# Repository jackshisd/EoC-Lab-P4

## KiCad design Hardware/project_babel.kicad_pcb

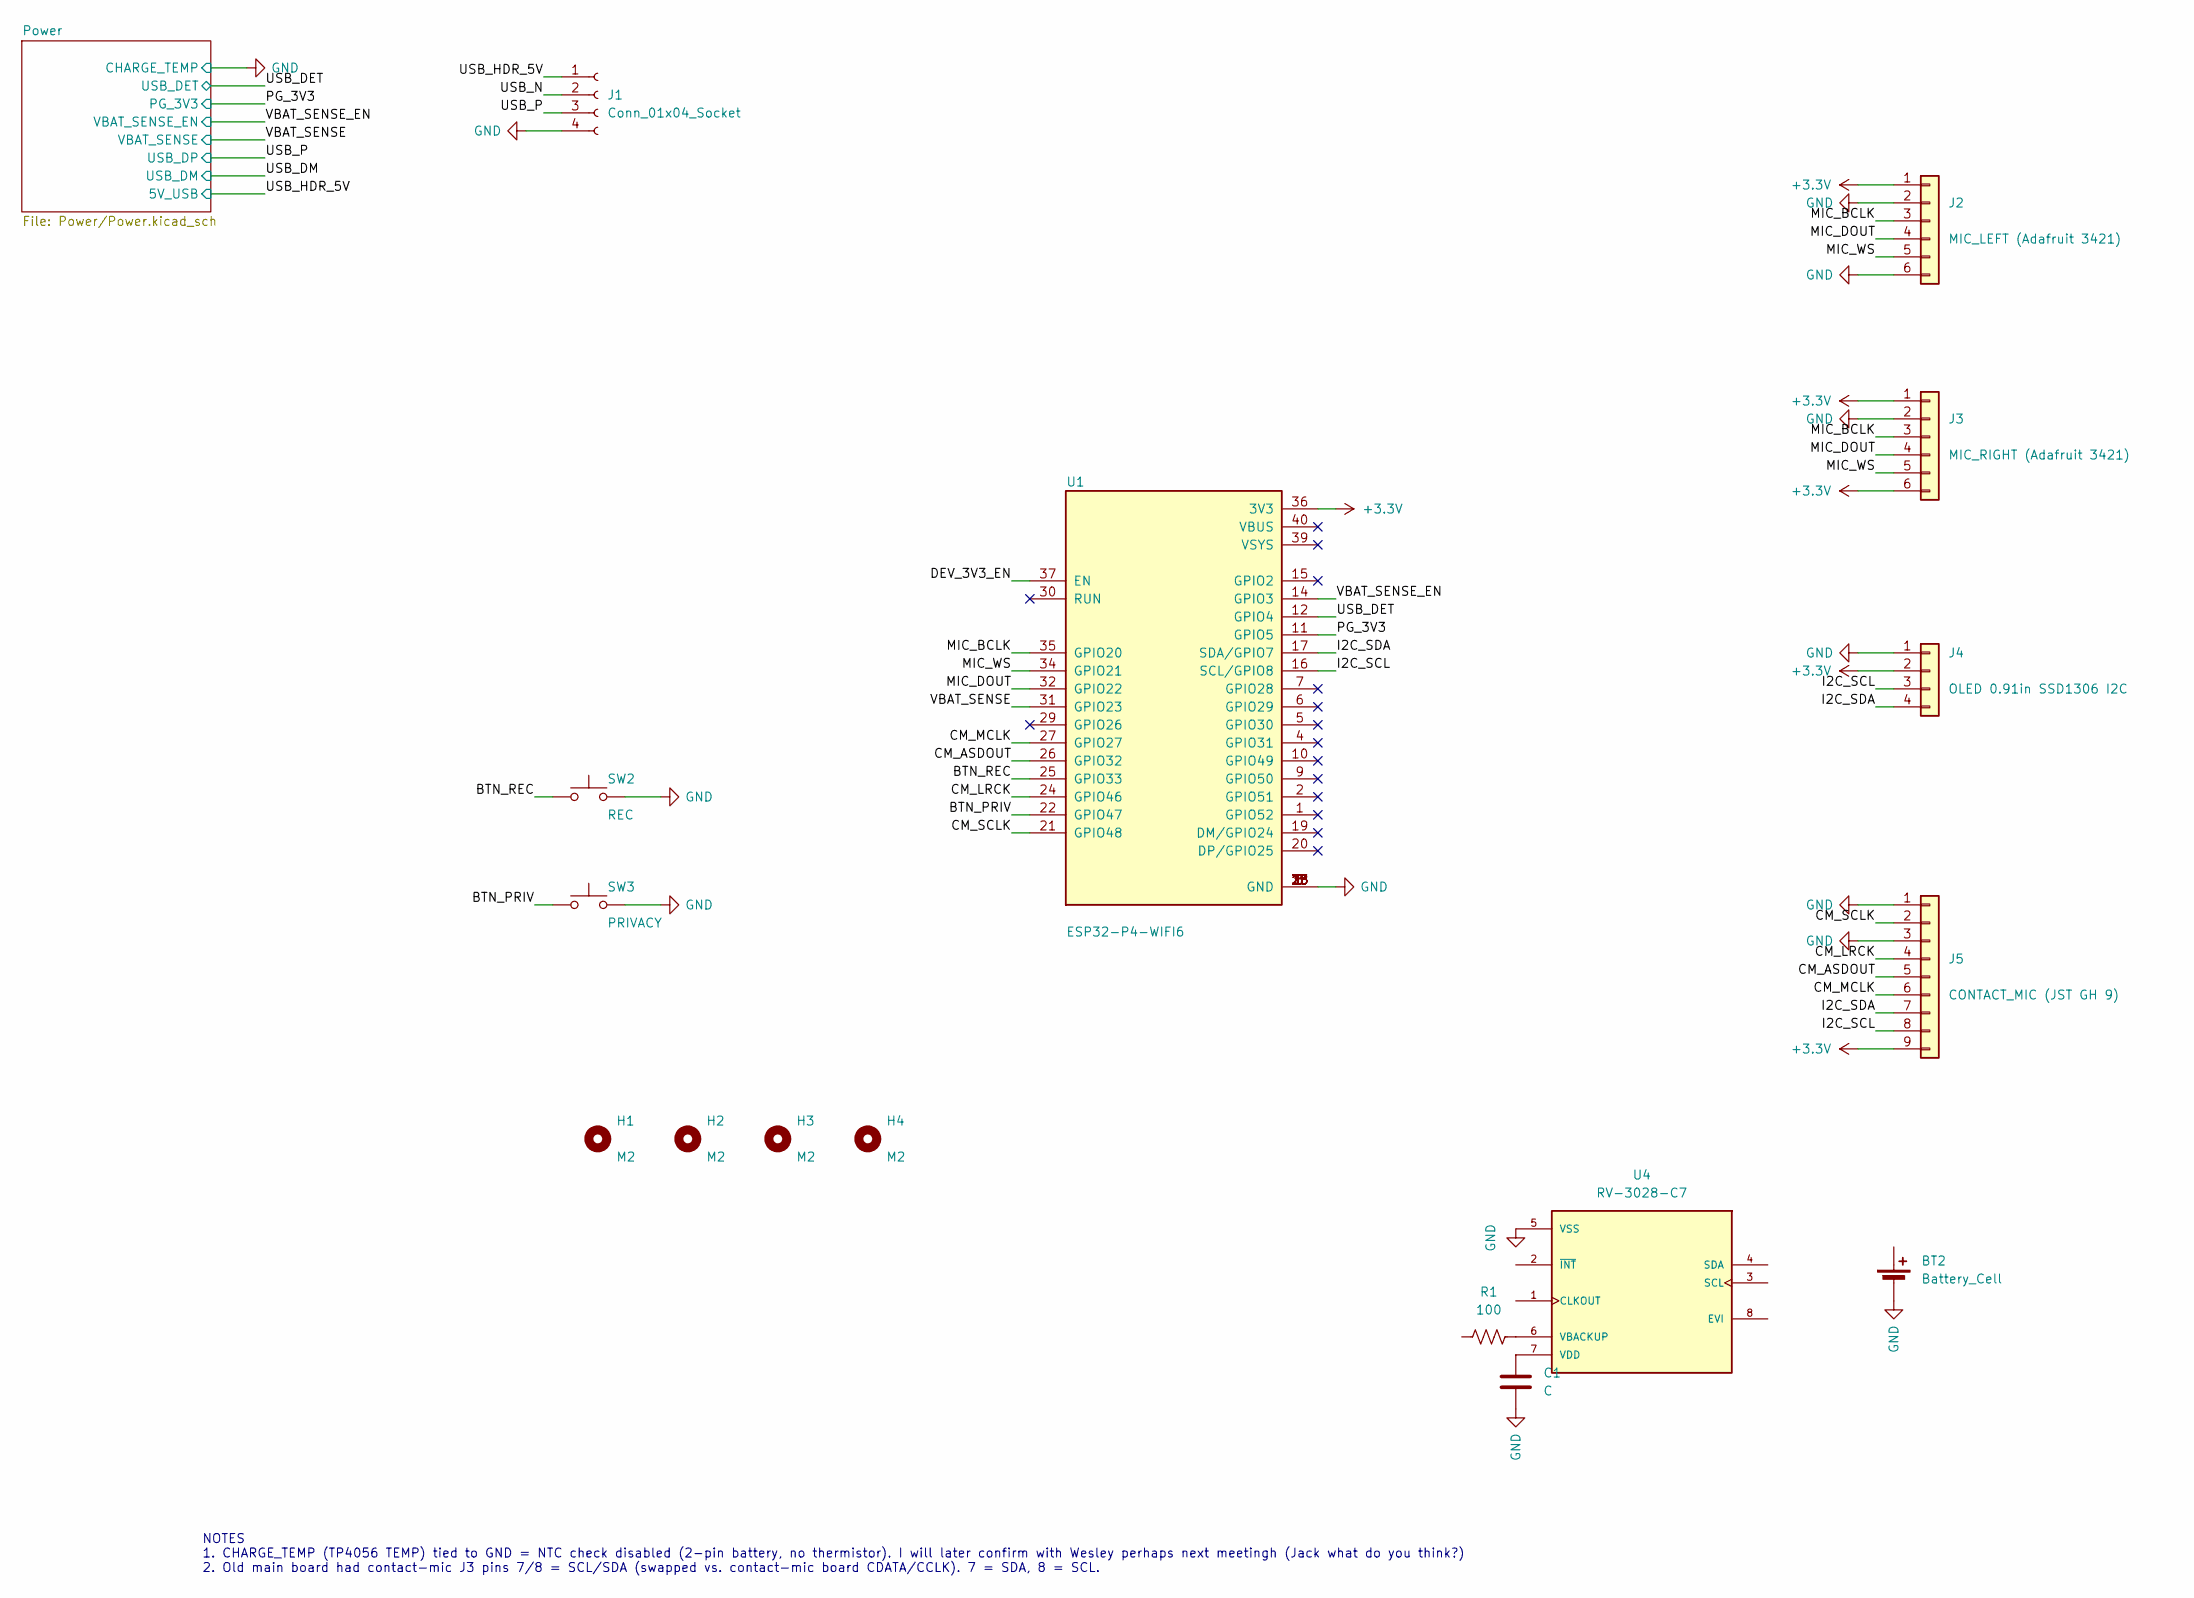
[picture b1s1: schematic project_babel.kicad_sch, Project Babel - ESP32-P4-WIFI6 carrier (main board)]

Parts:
BT2: Battery_Cell; BatteryHolder_Keystone_3000_1x12mm
C1: C
H1, H2, H3, H4: M2; MountingHole_2.2mm_M2
J1: Conn_01x04_Socket; PinHeader_1x04_P1.27mm_Vertical
J2: MIC_LEFT (Adafruit 3421); Adafruit_I2S_MEMS_Mic_Breakout_1x06_P2.54mm; MPN Adafruit 3421
J3: MIC_RIGHT (Adafruit 3421); Adafruit_I2S_MEMS_Mic_Breakout_1x06_P2.54mm; MPN Adafruit 3421
J4: OLED 0.91in SSD1306 I2C; SSD1306-0.91-OLED-4pin-128x32
J5: CONTACT_MIC (JST GH 9); JST_GH_SM09B-GHS-TB_1x09-1MP_P1.25mm_Horizontal; MPN JST SM09B-GHS-TB(LF)(SN)
R1: 100
SW2: REC; SW_SPST_PTS645Sx43SMTR92; MPN C&K PTS645SM43SMTR92 LFS (6x6 SMD)
SW3: PRIVACY; SW_SPST_PTS645Sx43SMTR92; MPN C&K PTS645SM43SMTR92 LFS (6x6 SMD)
U1: ESP32-P4-WIFI6; MODULE_ESP32-P4-WIFI6; MPN ESP32-P4-WIFI6
U4: RV-3028-C7; IC_RV-3028-C7; MPN RV-3028-C7

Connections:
+3.3V: J2.1, J3.1, J3.6, J4.2, J5.9, U1.36 (3V3); also elsewhere on the board
+5V_USB: J1.1; also elsewhere on the board
/BTN_PRIV: SW3.1, U1.22 (GPIO47)
/BTN_REC: SW2.1, U1.25 (GPIO33)
/CM_ASDOUT: J5.5, U1.26 (GPIO32)
/CM_LRCK: J5.4, U1.24 (GPIO46)
/CM_MCLK: J5.6, U1.27 (GPIO27)
/CM_SCLK: J5.2, U1.21 (GPIO48)
/DEV_3V3_EN: U1.37 (EN)
/I2C_SCL: J4.3, J5.8, U1.16 (SCL/GPIO8)
/I2C_SDA: J4.4, J5.7, U1.17 (SDA/GPIO7)
/MIC_BCLK: J2.3, J3.3, U1.35 (GPIO20)
/MIC_DOUT: J2.4, J3.4, U1.32 (GPIO22)
/MIC_WS: J2.5, J3.5, U1.34 (GPIO21)
/PG_3V3: U1.11 (GPIO5); also elsewhere on the board
/USB_DET: U1.12 (GPIO4); also elsewhere on the board
/USB_N: J1.2
/USB_P: J1.3; also elsewhere on the board
/VBAT_SENSE: U1.31 (GPIO23); also elsewhere on the board
/VBAT_SENSE_EN: U1.14 (GPIO3); also elsewhere on the board
GND: BT2.2 (-_2), C1.2, J1.4, J2.2, J2.6, J3.2, J4.1, J5.1, J5.3, SW2.2, SW3.2, U1.3 (GND), U1.8 (GND), U1.13 (GND), U1.18 (GND), U1.23 (GND), U1.28 (GND), U1.33 (GND), U1.38 (GND), U4.5 (VSS); also elsewhere on the board
unnamed: R1.2, U4.6 (VBACKUP)
unnamed: C1.1, U4.7 (VDD)

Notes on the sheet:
NOTES 1. CHARGE_TEMP (TP4056 TEMP) tied to GND = NTC check disabled (2-pin battery, no thermistor). I will later confirm with Wesley perhaps next meetingh (Jack what do you think?) 2. Old main board had contact-mic J3 pins 7/8 = SCL/SDA (swapped vs. contact-mic board CDATA/CCLK). 7 = SDA, 8 = SCL.

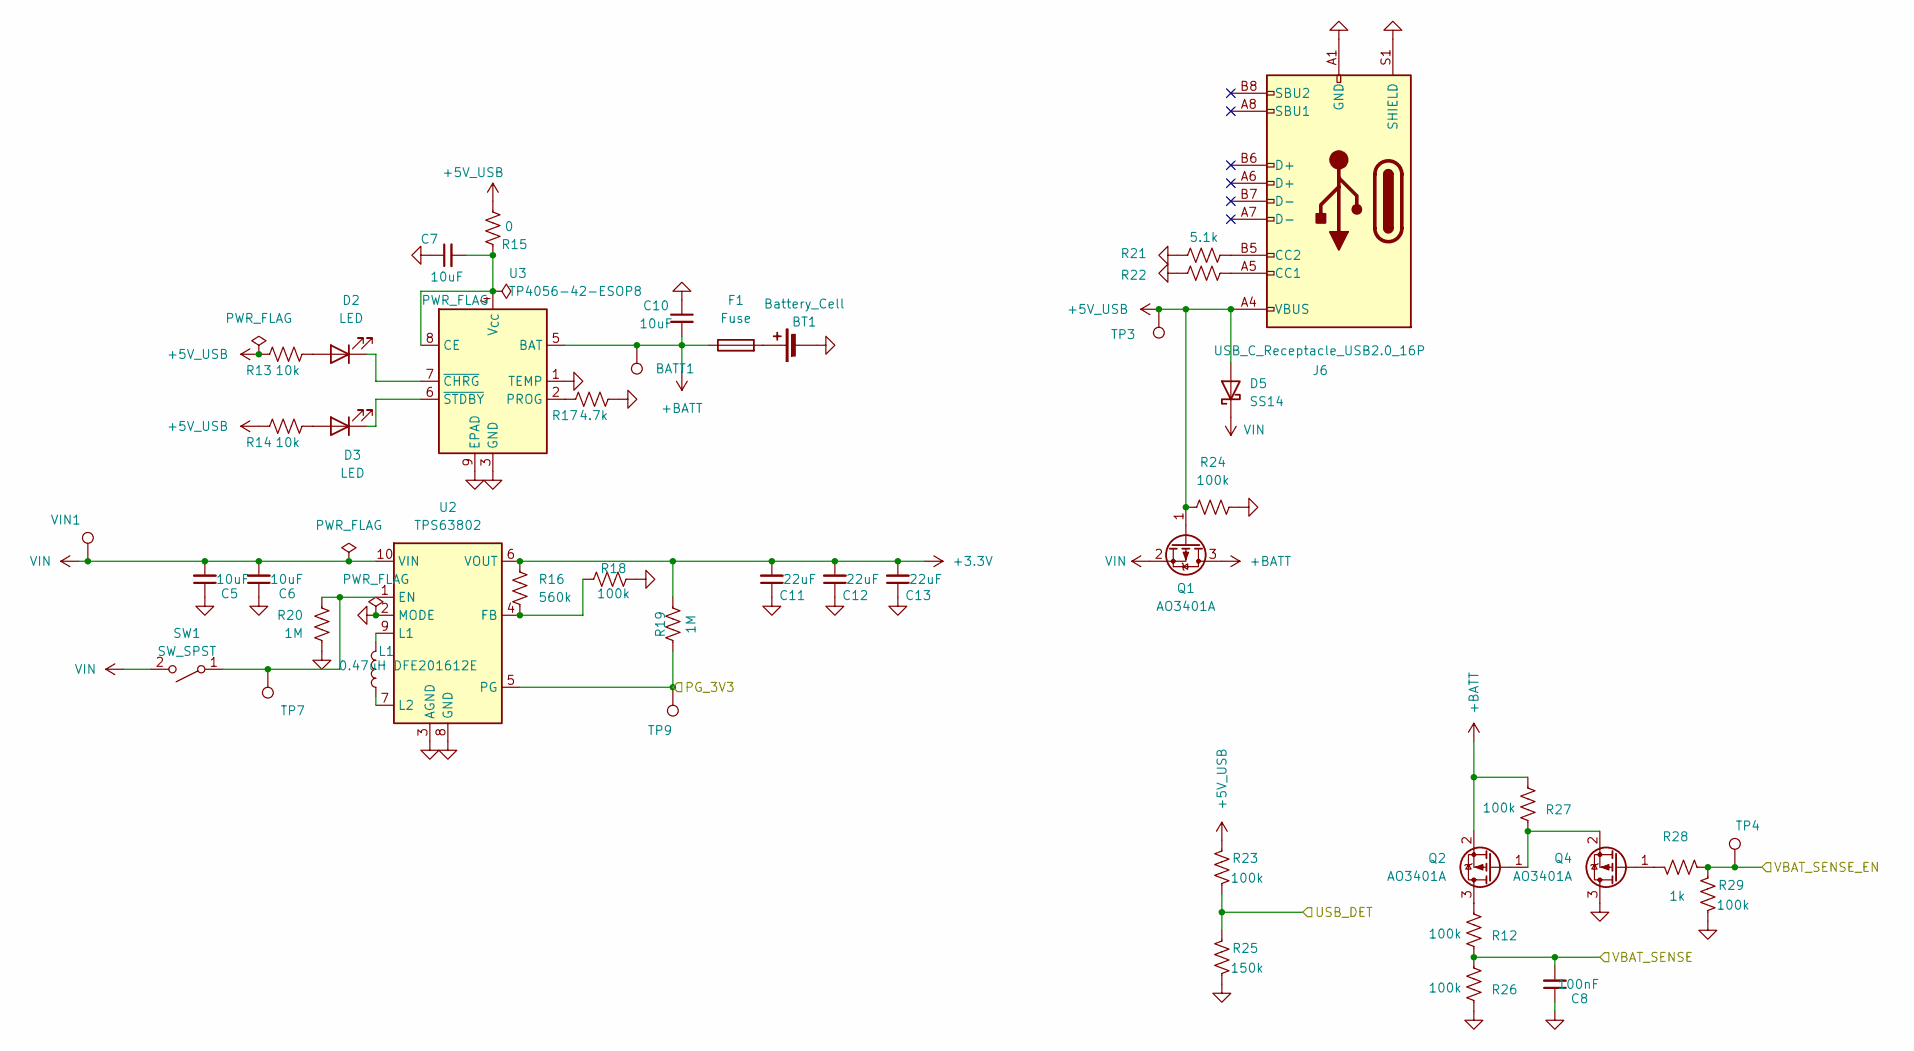
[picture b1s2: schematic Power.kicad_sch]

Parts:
BATT1: TestPoint; TestPoint_Pad_1.0x1.0mm
BT1: Battery_Cell; JST_PH_S2B-PH-K_1x02_P2.00mm_Horizontal
C5, C6: 10uF; C_0603_1608Metric
C7, C10: 10uF; C_0402_1005Metric
C8: 100nF; C_0603_1608Metric
C11, C12, C13: 22uF; C_0805_2012Metric
D2, D3: LED; LED_0603_1608Metric
D5: SS14; D_SMA
F1: Fuse; Fuse_1206_3216Metric
J6: USB_C_Receptacle_USB2.0_16P; USB_C_Receptacle_HRO_TYPE-C-31-M-12
L1: 0.47uH DFE201612E; L_0805_2012Metric
Q1, Q2, Q4: AO3401A; SOT-23
R12, R18, R23, R24, R26, R27, R29: 100k; R_0402_1005Metric
R13, R14: 10k; R_0402_1005Metric
R15: 0; R_0402_1005Metric
R16: 560k; R_0402_1005Metric
R17: 4.7k; R_0402_1005Metric
R19, R20: 1M; R_0402_1005Metric
R21, R22: 5.1k; R_0402_1005Metric
R25: 150k; R_0402_1005Metric
R28: 1k; R_0402_1005Metric
SW1: SW_SPST; PinHeader_1x03_P2.54mm_Vertical
TP3: TestPoint; PinHeader_1x01_P2.54mm_Vertical
TP4, TP7, TP9: TestPoint; TestPoint_Pad_1.0x1.0mm
U2: TPS63802
U3: TP4056-42-ESOP8; SOIC-8-1EP_3.9x4.9mm_P1.27mm_EP2.41x3.3mm_ThermalVias
VIN1: TestPoint; TestPoint_Pad_1.0x1.0mm

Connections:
+3.3V: C11.2, C12.2, C13.2, R16.2, R19.2, U2.6 (VOUT); also elsewhere on the board
+5V_USB: D5.2 (A), J6.A4 (VBUS), J6.A9 (VBUS), J6.B4 (VBUS), J6.B9 (VBUS), Q1.1 (G), R13.2, R14.2, R15.1, R23.2, R24.1, TP3.1 (1_1); also elsewhere on the board
+BATT: BATT1.1 (1_1), C10.2, F1.1, Q1.3 (D), Q2.2 (S), R27.1, U3.5 (BAT)
/PG_3V3: R19.1, TP9.1 (1_1), U2.5 (PG); also elsewhere on the board
/USB_DET: R23.1, R25.2; also elsewhere on the board
/USB_DM: J6.A7 (D-), J6.B7 (D-)
/USB_P: J6.A6 (D+), J6.B6 (D+); also elsewhere on the board
/VBAT_SENSE: C8.2, R12.2, R26.1; also elsewhere on the board
/VBAT_SENSE_EN: R28.1, R29.2, TP4.1 (1_1); also elsewhere on the board
GND: BT1.2 (-), C5.1, C6.1, C7.1, C8.1, C10.1, C11.1, C12.1, C13.1, J6.A1 (GND), J6.A12 (GND), J6.B1 (GND), J6.B12 (GND), J6.S1 (SHIELD), Q4.3 (D), R17.1, R18.1, R20.2, R21.2, R22.2, R24.2, R25.1, R26.2, R29.1, U2.2 (MODE), U2.3 (AGND), U2.8 (GND), U3.1 (TEMP), U3.3 (GND), U3.9 (EPAD); also elsewhere on the board
unnamed: BT1.1 (+), F1.2
unnamed: D2.2 (A), R13.1
unnamed: D2.1 (K), U3.7 (~CHRG)
unnamed: D3.2 (A), R14.1
unnamed: D3.1 (K), U3.6 (~STDBY)
unnamed: J6.A5 (CC1), R22.1
unnamed: J6.B5 (CC2), R21.1
unnamed: Q2.3 (D), R12.1
unnamed: Q2.1 (G), Q4.2 (S), R27.2
unnamed: Q4.1 (G), R28.2
unnamed: R20.1, SW1.1 (A), TP7.1 (1_1), U2.1 (EN)
unnamed: R16.1, R18.2, U2.4 (FB)
unnamed: L1.2, U2.9 (L1)
unnamed: L1.1, U2.7 (L2)
unnamed: C7.2, R15.2, U3.4 (V_{CC}), U3.8 (CE)
unnamed: R17.2, U3.2 (PROG)
VIN: C5.2, C6.2, D5.1 (K), Q1.2 (S), SW1.2 (B), U2.10 (VIN), VIN1.1 (1_1)

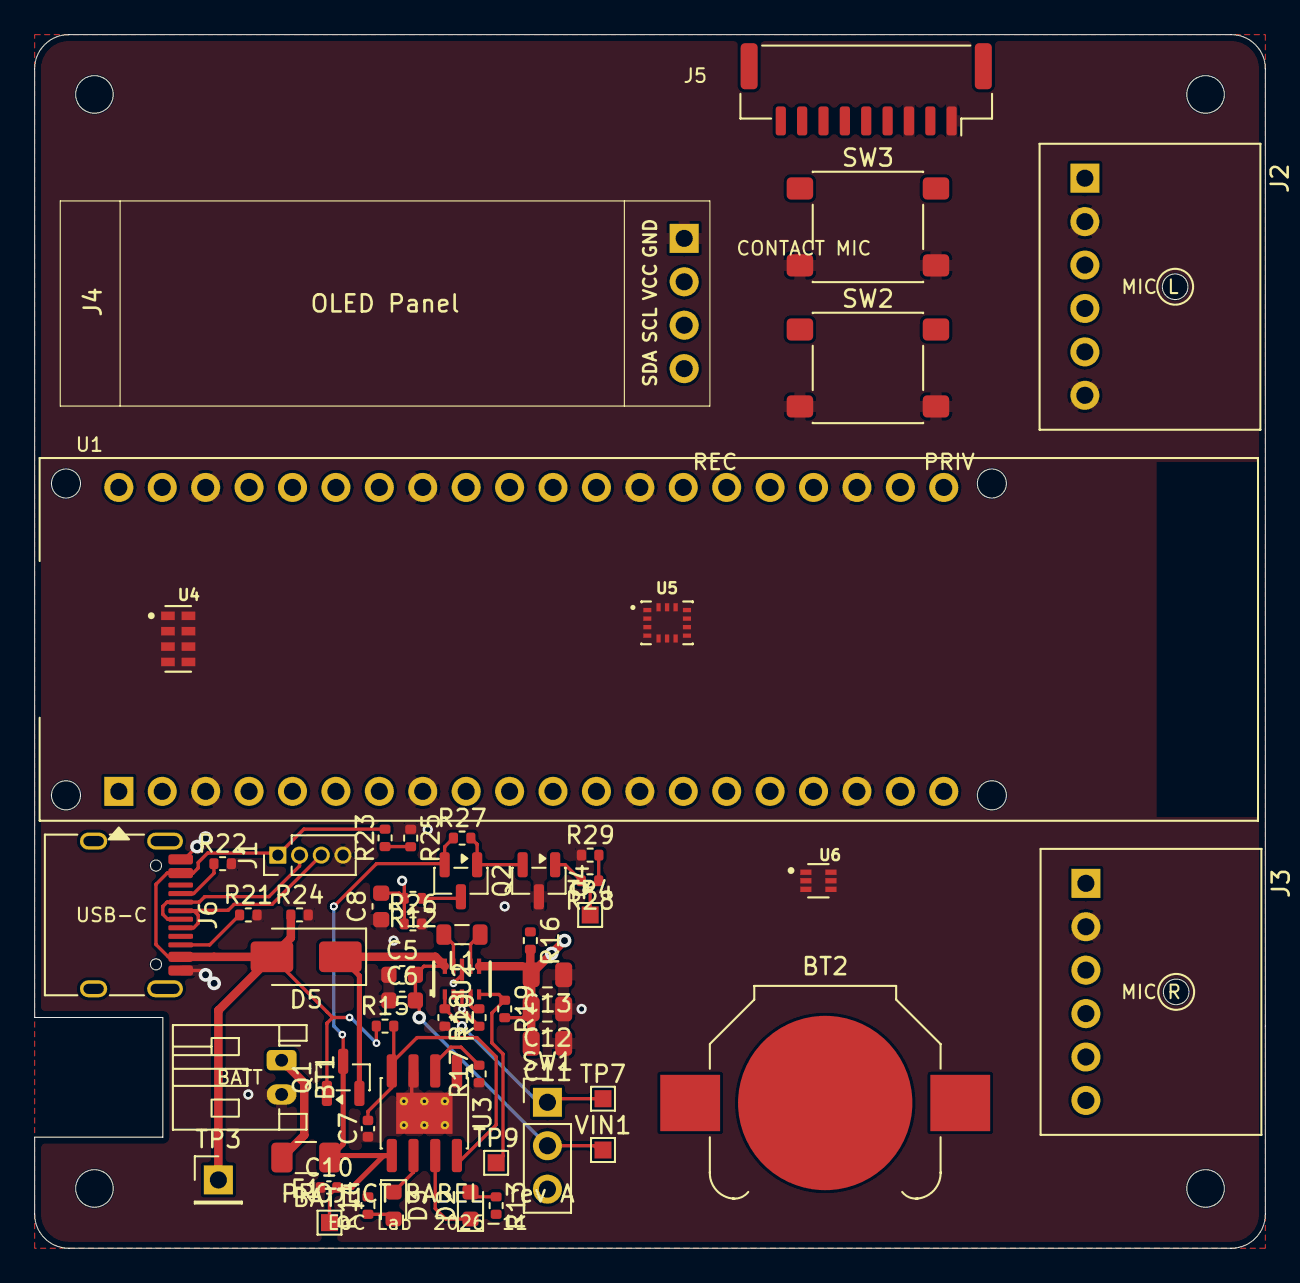
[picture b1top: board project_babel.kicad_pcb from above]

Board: 4 copper layers, 72.0 x 71.0 mm, 61 parts (0 on the bottom side), 38 nets.

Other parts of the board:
U5: BMI270; XDCR_BMI270
U6: TMP112AIDRLR; SOT50P160X60-6N

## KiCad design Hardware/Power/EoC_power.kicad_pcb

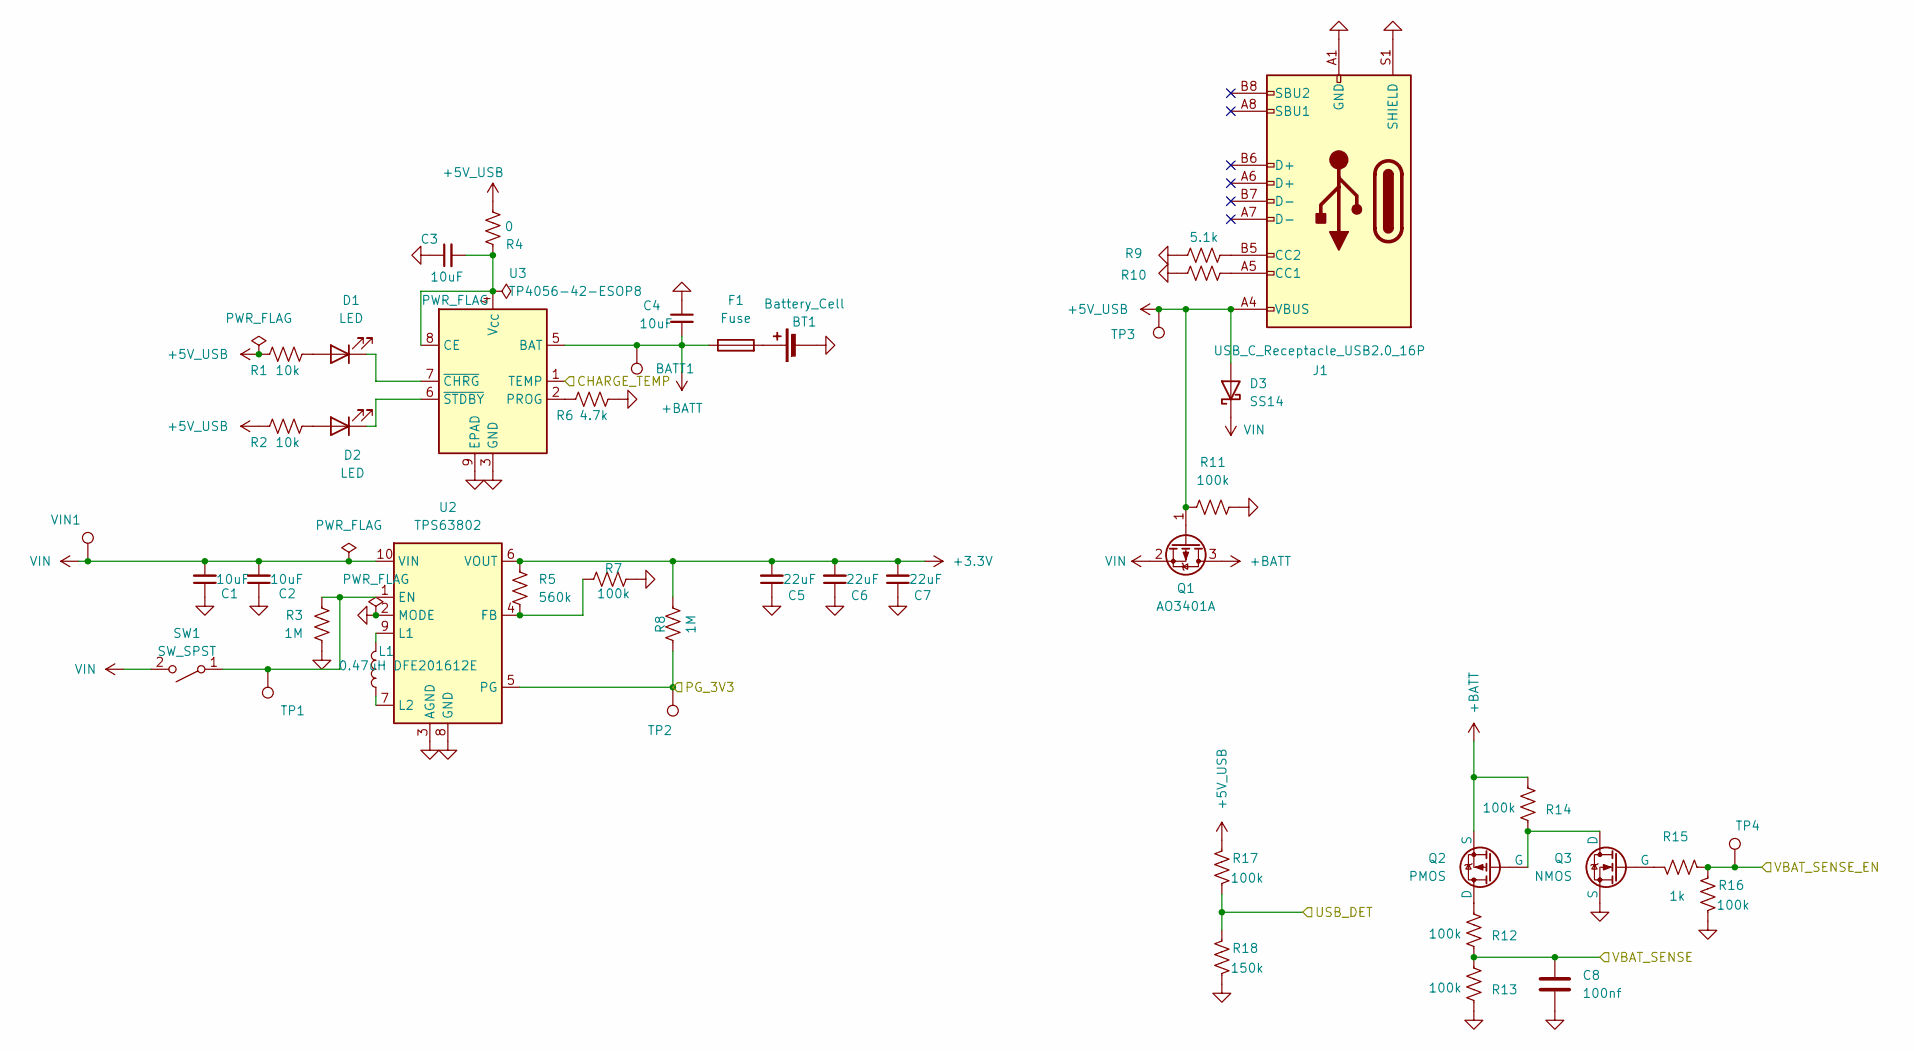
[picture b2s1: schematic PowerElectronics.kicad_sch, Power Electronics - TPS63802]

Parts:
BATT1: TestPoint; TestPoint_Pad_1.0x1.0mm
BT1: Battery_Cell; JST_PH_S2B-PH-K_1x02_P2.00mm_Horizontal
C1, C2: 10uF; C_0603_1608Metric
C3, C4: 10uF; C_0402_1005Metric
C5, C6, C7: 22uF; C_0805_2012Metric
C8: 100nf; C_0603_1608Metric
D1, D2: LED; LED_0603_1608Metric
D3: SS14; D_SMA
F1: Fuse; Fuse_1206_3216Metric
J1: USB_C_Receptacle_USB2.0_16P; USB_C_Receptacle_HRO_TYPE-C-31-M-12
L1: 0.47uH DFE201612E; L_0805_2012Metric_Pad1.05x1.20mm_HandSolder
Q1: AO3401A; SOT-23
Q2: PMOS; SOT-23
Q3: NMOS; SOT-23
R1, R2: 10k; R_0402_1005Metric
R3, R8: 1M; R_0402_1005Metric
R4: 0; R_0402_1005Metric
R5: 560k; R_0402_1005Metric
R6: 4.7k; R_0402_1005Metric
R7, R11, R12, R13, R14, R16, R17: 100k; R_0402_1005Metric
R9, R10: 5.1k; R_0402_1005Metric
R15: 1k; R_0402_1005Metric
R18: 150k; R_0402_1005Metric
SW1: SW_SPST; PinHeader_1x03_P2.54mm_Vertical
TP1, TP2, TP4: TestPoint; TestPoint_Pad_1.0x1.0mm
TP3: TestPoint; PinHeader_1x01_P2.54mm_Vertical
U2: TPS63802; DLA0010A
U3: TP4056-42-ESOP8; SOIC-8-1EP_3.9x4.9mm_P1.27mm_EP2.41x3.3mm_ThermalVias
VIN1: TestPoint; TestPoint_Pad_1.0x1.0mm

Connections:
+3.3V: C5.2, C6.2, C7.2, R5.2, R8.2, U2.6 (VOUT); also elsewhere on the board
+5V_USB: D3.2 (A), J1.A4 (VBUS), J1.A9 (VBUS), J1.B4 (VBUS), J1.B9 (VBUS), Q1.1 (G), R1.2, R2.2, R4.1, R11.1, R17.2, TP3.1
+BATT: BATT1.1, C4.2, F1.1, Q1.3 (D), Q2.3 (S), R14.1, U3.5 (BAT)
/PG_3V3: R8.1, TP2.1, U2.5 (PG); also elsewhere on the board
/USB_DET: R17.1, R18.2; also elsewhere on the board
/VBAT_SENSE: C8.1, R12.2, R13.1; also elsewhere on the board
/VBAT_SENSE_EN: R15.1, R16.2, TP4.1; also elsewhere on the board
GND: BT1.2 (-), C1.1, C2.1, C3.1, C4.1, C5.1, C6.1, C7.1, C8.2, J1.A1 (GND), J1.A12 (GND), J1.B1 (GND), J1.B12 (GND), J1.S1 (SHIELD), J1.SH, Q3.3 (S), R3.2, R6.1, R7.1, R9.2, R10.2, R11.2, R13.2, R16.1, R18.1, U2.2 (MODE), U2.3 (AGND), U2.8 (GND), U3.1 (TEMP), U3.3 (GND), U3.9 (EPAD)
unnamed: BT1.1 (+), F1.2
unnamed: D1.2 (A), R1.1
unnamed: D1.1 (K), U3.7 (~CHRG)
unnamed: D2.2 (A), R2.1
unnamed: D2.1 (K), U3.6 (~STDBY)
unnamed: J1.A5 (CC1), R10.1
unnamed: J1.B5 (CC2), R9.1
unnamed: R3.1, SW1.1 (A), TP1.1, U2.1 (EN)
unnamed: R5.1, R7.2, U2.4 (FB)
unnamed: L1.2, U2.9 (L1)
unnamed: L1.1, U2.7 (L2)
unnamed: C3.2, R4.2, U3.4 (V_{CC}), U3.8 (CE)
unnamed: R6.2, U3.2 (PROG)
VBAT_SENSE_GATE: Q2.2 (G), Q3.1 (D), R14.2
VBAT_SENSE_GATE_DRIVE: Q3.2 (G), R15.2
VBAT_SENSE_SWITCHED: Q2.1 (D), R12.1
VIN: C1.2, C2.2, D3.1 (K), Q1.2 (S), SW1.2 (B), U2.10 (VIN), VIN1.1

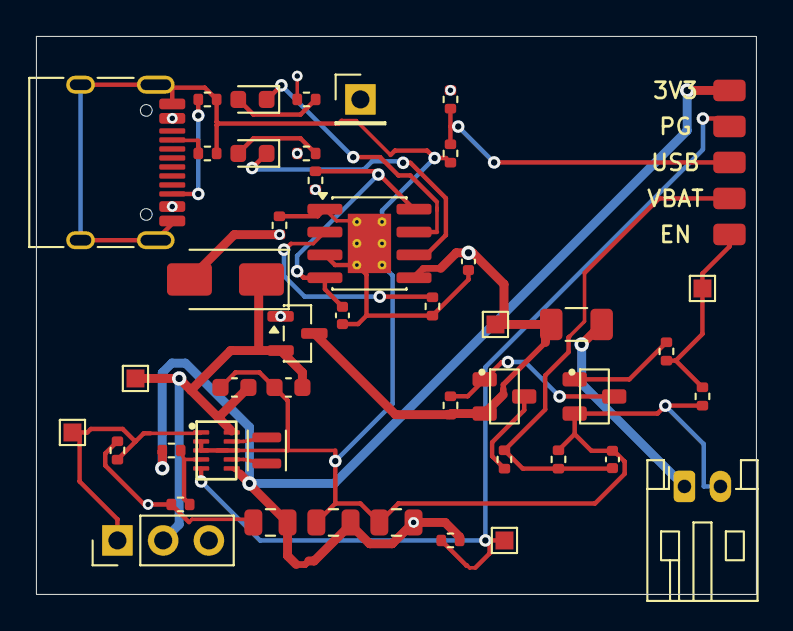
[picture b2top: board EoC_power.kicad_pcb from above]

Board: 4 copper layers, 40.0 x 31.0 mm, 46 parts (0 on the bottom side), 25 nets.

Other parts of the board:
IF1: POWER_TO_MAIN_BOARD

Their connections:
+3.3V: IF1.1; also elsewhere on the board
/PG_3V3: IF1.2; also elsewhere on the board
/USB_DET: IF1.3; also elsewhere on the board
/VBAT_SENSE: IF1.4; also elsewhere on the board
/VBAT_SENSE_EN: IF1.5; also elsewhere on the board
